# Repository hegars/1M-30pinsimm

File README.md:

# 1M-30pinsimm

KiCAD design for a 1MByte 30 pin SIMM Fast Page Mode Dynamic Random Access Memory Module Design

WORK IN PROGRESS - Dont let your blue smoke out.

## Real Boards

Boards back from JLCPCB

Seated in test socket fine, aliginmet is great

## Test Chips

Donor 72pin dual sided ram, 99cent ebay find which has enough chips for 8 boards.

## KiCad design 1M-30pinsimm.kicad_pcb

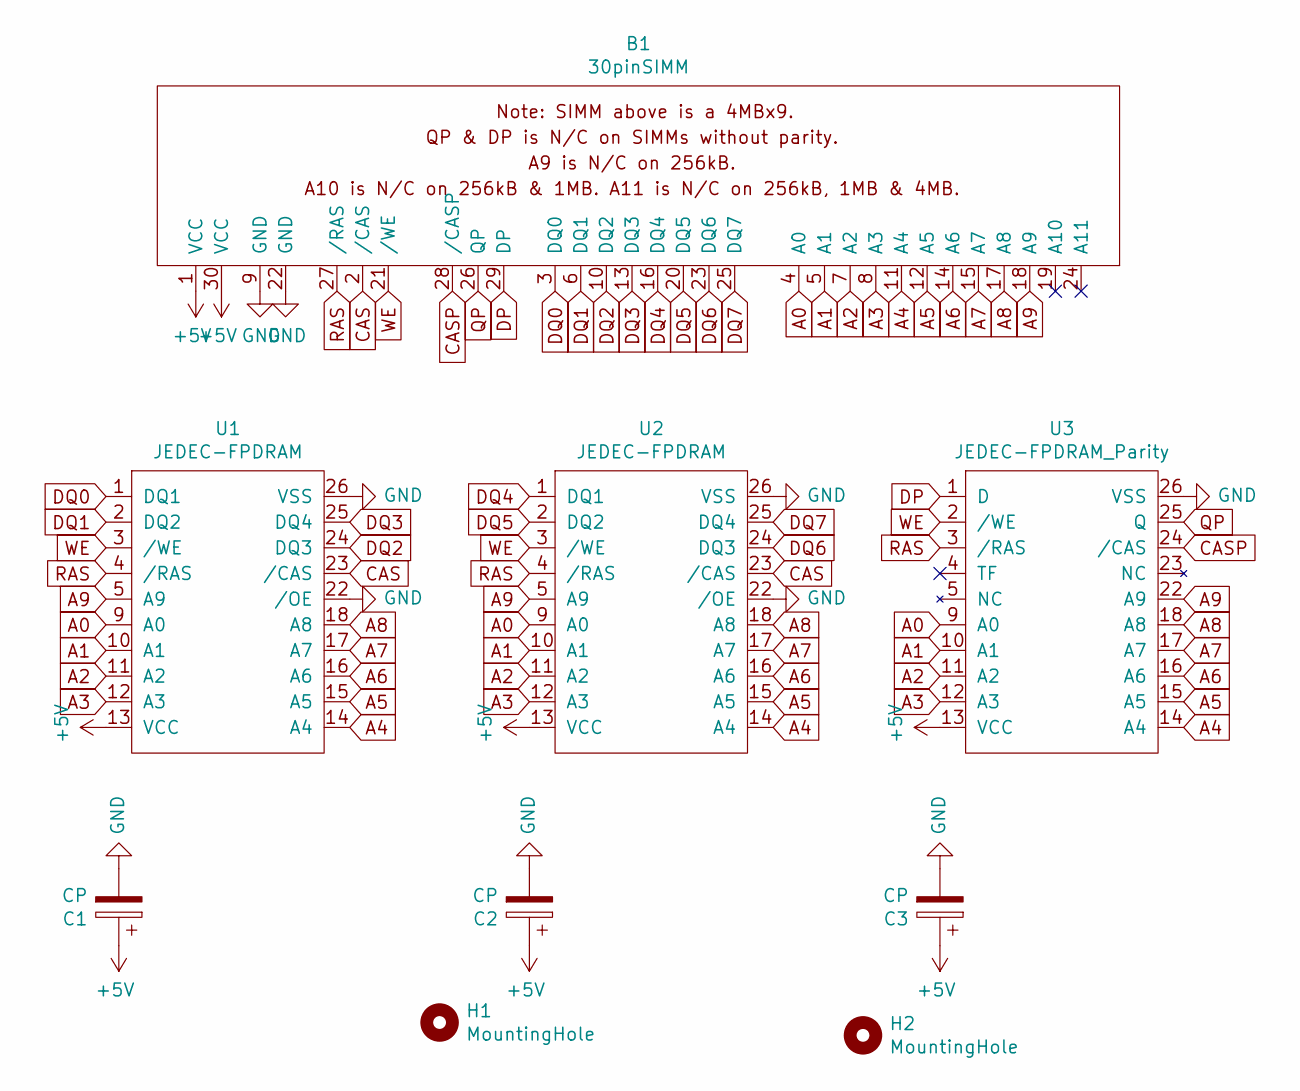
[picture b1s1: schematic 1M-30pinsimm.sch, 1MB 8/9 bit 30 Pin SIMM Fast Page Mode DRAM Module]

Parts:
B1: 30pinSIMM
C1, C2, C3: CP; C_0805_HandSoldering
H1, H2: MountingHole; MountingHole_3.2mm_M3
U1, U2: JEDEC-FPDRAM; SOJ-20
U3: JEDEC-FPDRAM_Parity; SOJ-20

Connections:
+5V: B1.1 (VCC), B1.30 (VCC), C1.1, C2.1, C3.1, U1.13 (VCC), U2.13 (VCC), U3.13 (VCC)
A0: B1.4 (A0), U1.9 (A0), U2.9 (A0), U3.9 (A0)
A1: B1.5 (A1), U1.10 (A1), U2.10 (A1), U3.10 (A1)
A2: B1.7 (A2), U1.11 (A2), U2.11 (A2), U3.11 (A2)
A3: B1.8 (A3), U1.12 (A3), U2.12 (A3), U3.12 (A3)
A4: B1.11 (A4), U1.14 (A4), U2.14 (A4), U3.14 (A4)
A5: B1.12 (A5), U1.15 (A5), U2.15 (A5), U3.15 (A5)
A6: B1.14 (A6), U1.16 (A6), U2.16 (A6), U3.16 (A6)
A7: B1.15 (A7), U1.17 (A7), U2.17 (A7), U3.17 (A7)
A8: B1.17 (A8), U1.18 (A8), U2.18 (A8), U3.18 (A8)
A9: B1.18 (A9), U1.5 (A9), U2.5 (A9), U3.22 (A9)
CAS: B1.2 (/CAS), U1.23 (/CAS), U2.23 (/CAS)
CASP: B1.28 (/CASP), U3.24 (/CAS)
DP: B1.29 (DP), U3.1 (D)
DQ0: B1.3 (DQ0), U1.1 (DQ1)
DQ1: B1.6 (DQ1), U1.2 (DQ2)
DQ2: B1.10 (DQ2), U1.24 (DQ3)
DQ3: B1.13 (DQ3), U1.25 (DQ4)
DQ4: B1.16 (DQ4), U2.1 (DQ1)
DQ5: B1.20 (DQ5), U2.2 (DQ2)
DQ6: B1.23 (DQ6), U2.24 (DQ3)
DQ7: B1.25 (DQ7), U2.25 (DQ4)
GND: B1.9 (GND), B1.22 (GND), C1.2, C2.2, C3.2, U1.22 (/OE), U1.26 (VSS), U2.22 (/OE), U2.26 (VSS), U3.26 (VSS)
QP: B1.26 (QP), U3.25 (Q)
RAS: B1.27 (/RAS), U1.4 (/RAS), U2.4 (/RAS), U3.3 (/RAS)
WE: B1.21 (/WE), U1.3 (/WE), U2.3 (/WE), U3.2 (/WE)

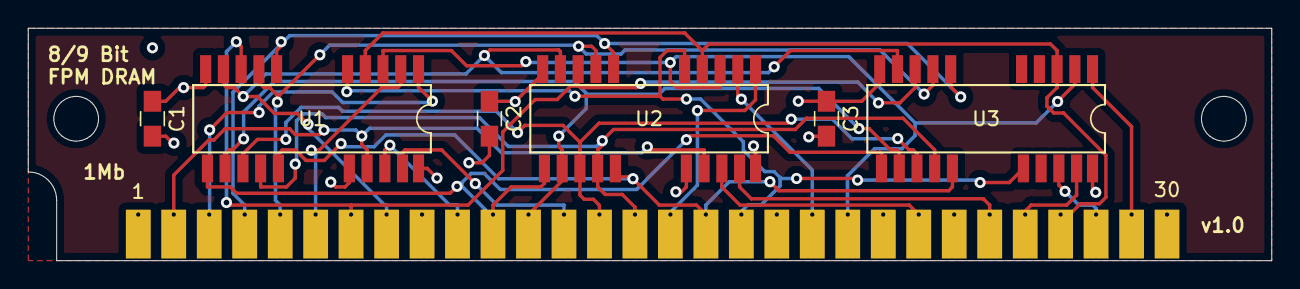
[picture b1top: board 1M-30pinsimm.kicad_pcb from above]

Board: 4 copper layers, 89.0 x 16.6 mm, 9 parts (0 on the bottom side), 26 nets.

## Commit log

2021-01-12 completed autorouting
2021-01-12 generate gerbers
2021-01-12 cleaned up tracks
2021-01-12 regenerate gerbers
2021-01-12 update title frame
2021-01-12 add ignore
2021-01-12 change caps
2021-01-12 update gerbers
2021-01-12 added datasheets
2021-02-24 added pictures
2021-02-24 real boards
2021-02-24 donor chips
